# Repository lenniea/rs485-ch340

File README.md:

# RS485-CH340

## PCB

## Schematic

The BOM is in the doc folder.

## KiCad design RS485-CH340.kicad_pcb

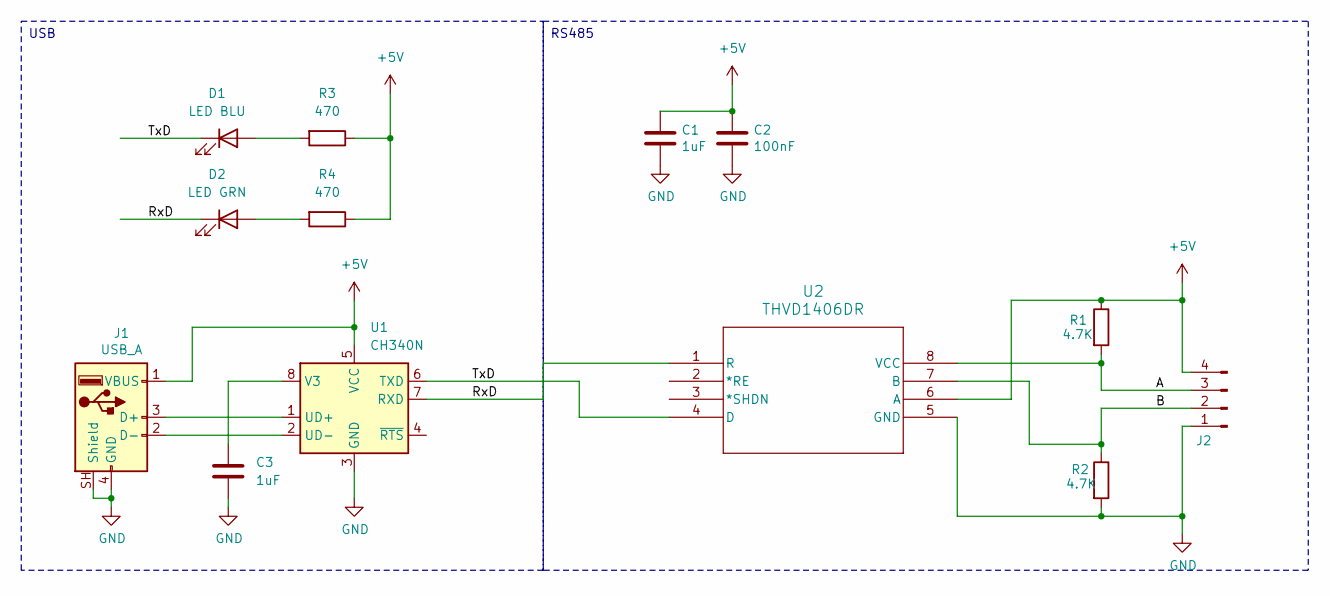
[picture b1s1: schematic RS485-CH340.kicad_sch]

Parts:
C1, C3: 1uF; C_0603_1608Metric_Pad1.08x0.95mm_HandSolder
C2: 100nF; C_0603_1608Metric_Pad1.08x0.95mm_HandSolder
D1: LED BLU; LED_0603_1608Metric_Pad1.05x0.95mm_HandSolder
D2: LED GRN; LED_0603_1608Metric_Pad1.05x0.95mm_HandSolder
J1: USB_A; USB_A_CNCTech_1001-011-01101_Horizontal
J2: Conn_01x04_Pin; PinHeader_1x04_P2.54mm_Horizontal
R1, R2: 4.7K; R_0603_1608Metric_Pad0.98x0.95mm_HandSolder
R3, R4: 470; R_0603_1608Metric_Pad0.98x0.95mm_HandSolder
U1: CH340N; JEITA_SOIC-8_3.9x4.9mm_P1.27mm
U2: THVD1406DR; SOIC-8_5.3x6.2mm_P1.27mm

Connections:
+5V: C1.1, C2.1, J1.1 (VBUS), J2.4, R1.1, R3.1, R4.1, U1.5 (VCC), U2.6 (A)
/A: J2.3, R1.2, U2.8 (VCC)
/B: J2.2, R2.1, U2.7 (B)
/RxD: D2.1 (K), U1.7 (RXD), U2.1 (R)
/TxD: D1.1 (K), U1.6 (TXD), U2.4 (D)
GND: C1.2, C2.2, C3.2, J1.4 (GND), J1.SH (Shield), J2.1, R2.2, U1.3 (GND), U2.5 (GND)
unnamed: D1.2 (A), R3.2
unnamed: D2.2 (A), R4.2
unnamed: J1.3 (D+), U1.1 (UD+)
unnamed: J1.2 (D-), U1.2 (UD-)
unnamed: C3.1, U1.8 (V3)

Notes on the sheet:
USB
RS485

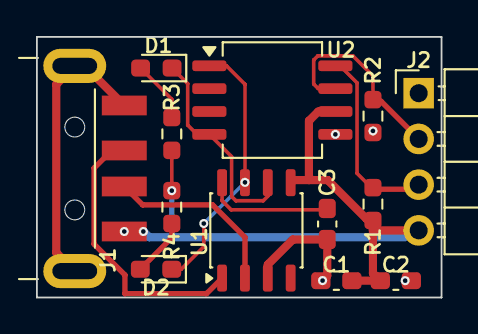
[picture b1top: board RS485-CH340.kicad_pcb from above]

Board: 2 copper layers, 22.5 x 14.5 mm, 13 parts (0 on the bottom side), 11 nets.

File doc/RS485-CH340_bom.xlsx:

Reference | Qty | Value | Footprint | Datasheet
C1,C3 | 2 | 1uF | Capacitor_SMD:C_0603_1608Metric_Pad1.08x0.95mm_HandSolder | ~
C2 | 1 | 100nF | Capacitor_SMD:C_0603_1608Metric_Pad1.08x0.95mm_HandSolder | ~
D1 | 1 | LED BLU | LED_SMD:LED_0603_1608Metric_Pad1.05x0.95mm_HandSolder
D2 | 1 | LED GRN | LED_SMD:LED_0603_1608Metric_Pad1.05x0.95mm_HandSolder
J1 | 1 | USB_A | Connector_USB:USB_A_CNCTech_1001-011-01101_Horizontal | http://cnctech.us/pdfs/1001-011-01101.pdf
J2 | 1 | Conn_01x04_Pin | Connector_PinHeader_2.54mm:PinHeader_1x04_P2.54mm_Horizontal
R1,R2 | 2 | 4.7K | Resistor_SMD:R_0603_1608Metric_Pad0.98x0.95mm_HandSolder
R3,R4 | 2 | 470 | Resistor_SMD:R_0603_1608Metric_Pad0.98x0.95mm_HandSolder
U1 | 1 | CH340N | Package_SO:JEITA_SOIC-8_3.9x4.9mm_P1.27mm | https://aitendo3.sakura.ne.jp/aitendo_data/product_img/ic/in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
U2 | 1 | THVD1406DR | Package_SO:SOIC-8_5.3x6.2mm_P1.27mm | https://www.ti.com/lit/gpn/thvd1406
